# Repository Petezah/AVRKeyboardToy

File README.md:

AVR Keyboard Toy
================

This is beginning as a fork of TinyBasic Plus, whose description
is below.  The intention is to build a self-contained computer-in-
a-keyboard device using an old PS/2 Keyboard and an AVR-based
microcontroller board, outputting display output to a visual display
output--in my case, a 160x160 SPI TFT display.  

The description for TinyBasic Plus is as follows:

# TinyBasic Plus

A C implementation of Tiny Basic, with a focus on support for
Arduino.  It was originally written by Gordon Brandly in the form
of "68000 Tiny Basic", and then ported to C by Michael Field as
"Arduino Basic", though still called "Tiny Basic" in the source
files.

TinyBasic Plus is an extension and modification upon the original
"Tiny Basic" by adding support for a few more devices, configurable
at build time.  It is designed for use on the Arduino, although
builds will soon be easily possible for other platforms through
command line makefiles.  Provided is a makefile that builds for 
unix-ey type OSes.  It has only been tested for Darwin (OS X).

Features added include support for fileio (SD Library), autorunning
a program from the SD card, smaller footprint (PROGMEM), support
for pin data IO, and support for the on-chip EEProm storage for your
program. 

# Full list of supported statements and functions

## System
- BYE		- *exits Basic, soft reboot on Arduino*
- END 		- *stops execution from the program, also "STOP"*
- MEM		- *displays memory usage statistics*
- NEW		- *clears the current program*
- RUN		- *executes the current program*

## File IO/SD Card
- FILES		- 	*lists the files on the SD card*
- LOAD filename.bas	- *loads a file from the SD card*
- CHAIN filename.bas - *equivalent of: new, load filename.bas, run*
- SAVE filename.bas	- *saves the current program to the SD card, overwriting*

## EEProm - nonvolatile on-chip storage
- EFORMAT	- clears the EEProm memory
- ELOAD		- load the program in from EEProm
- ESAVE		- save the current program to the EEProm
- ELIST		- print out the contents of EEProm
- ECHAIN	- load the program from EEProm and run it

## IO, Documentation
- PEEK( address )	- *get a value in memory* (unimplemented)
- POKE address		- *set a value in memory* (unimplemented)
- PRINT expression	- *print out the expression, also "?"*
- REM stuff		- *remark/comment, also "'"*

## Expressions, Math
- A=V, LET A=V	- *assign value to a variable*
- +, -, \*, / - *Math*
- <,<=,=,<>,!=,>=,> - *Comparisons*
- ABS( expression )  - *returns the absolute value of the expression*
- RSEED( v ) - *sets the random seed to v*
- RND( m ) - *returns a random number from 0 to m*

## Control
- IF expression statement - *perform statement if expression is true*
- FOR variable = start TO end	- *start for block*
- FOR variable = start TO end STEP value - *start for block with step*
- NEXT - *end of for block*
- GOTO linenumber - *continue execution at this line number*
- GOSUB linenumber - *call a subroutine at this line number*
- RETURN	- *return from a subroutine*

## Pin IO 
- DELAY	timems*- wait (in milliseconds)*
- DWRITE pin,value - *set pin with a value (HIGH,HI,LOW,LO)*
- AWRITE pin,value - *set pin with analog value (pwm) 0..255*
- DREAD( pin ) - *get the value of the pin* 
- AREAD( analogPin ) - *get the value of the analog pin*

NOTE: "PINMODE" command removed as of version 0.11

## Sound - Piezo wired with red/+ on pin 5 and black/- to ground
- TONE freq,timems - play "freq" for "timems" milleseconds (1000 = 1 second)
- TONEW freq,timems - same as above, but also waits for it to finish
- NOTONE - stop playback of all playing tones

NOTE: TONE commands are by default disabled

# Example programs

Here are a few example programs to get you started...

## Blink

hook up an LED between pin 3 and ground

	10 FOR A=0 TO 10
	20 DWRITE 3, HIGH
	30 DELAY 250
	40 DWRITE 3, LOW
	50 DELAY 250
	60 NEXT A

## Fade

hook up an LED between pin 3 and ground

	10 FOR A=0 TO 10
	20 FOR B=0 TO 255
	30 AWRITE 3, B
	40 DELAY 10
	50 NEXT B
	60 FOR B=255 TO 0 STEP -1
	70 AWRITE 3, B
	80 DELAY 10
	90 NEXT B
	100 NEXT A

## LED KNOB

hook up a potentiometeter between analog 2 and ground, led from digital 3 and ground.  If knob is at 0, it stops

	10 A = AREAD( 2 )
	20 PRINT A
	30 B = A / 4
	40 AWRITE 3, B
	50 IF A == 0 GOTO 100
	60 GOTO 10
	100 PRINT "Done."

## ECHAIN example

Write a small program, store it in EEPROM.  We'll show that variables don't
get erased when chaining happens

	EFORMAT
	10 A = A + 2
	20 PRINT A
	30 PRINT "From eeprom!"
	40 IF A = 12 GOTO 100
	50 PRINT "Shouldn't be here."
	60 END
	100 PRINT "Hi!"

Then store it in EEProm

	ESAVE

Now, create a new program in main memory and run it

	NEW
	10 A = 10
	20 PRINT A
	30 PRINT "From RAM!"
	40 ECHAIN

List both, and run

	ELIST
	LIST
	RUN

# Device Support
## Current
- Arduino - ATMega 168 (~100 bytes available)
- Arduino - ATMega 368 (~1100 bytes available)
- SD cards (via SD Library, for FILES, LOAD, SAVE commands, uses 9k of ROM)
- EEProm (via EEProm Library, uses 500 bytes of ROM)
- Serial IO - command console

## Future
- PS2 Keyboard for standalone use (maybe)
- Graphics support via common function names and ANSI/ReGIS escape codes

# Known Quirks and Limitations
- If LOAD or SAVE are called, FILES fails subsequent listings
- SD cards are not hot-swappable. A reset is required between swaps.

# Authors and Contributors

- Tiny Basic 68k - Gordon Brandly [Project Page (via archive.org)](https://web.archive.org/web/20170306113457/http://members.shaw.ca:80/gbrandly/68ktinyb.html)
- Arduino Basic / Tiny Basic C - Michael Field [Project Page](http://hamsterworks.co.nz/mediawiki/index.php/Arduino_Basic)
- Tiny Basic Plus - Scott Lawrence <yorgle@gmail.com> [Github Page](http://github.com/BleuLlama/TinyBasicPlus)

- Jurg Wullschleger - Fix for unary operations and whitespace in expressions

- AVR Keyboard Toy - Peter Dunshee <peterdun@outlook.com> [Github Page](https://github.com/Petezah/AVRKeyboardToy)

# Links
- [Arduino Microcontroller](http://arduino.cc)

# MIT License

Copyright (c) 2012-2013

Permission is hereby granted, free of charge, to any person obtaining a copy of this software and associated documentation files (the "Software"), to deal in the Software without restriction, including without limitation the rights to use, copy, modify, merge, publish, distribute, sublicense, and/or sell copies of the Software, and to permit persons to whom the Software is furnished to do so, subject to the following conditions:

The above copyright notice and this permission notice shall be included in all copies or substantial portions of the Software.

THE SOFTWARE IS PROVIDED "AS IS", WITHOUT WARRANTY OF ANY KIND, EXPRESS OR IMPLIED, INCLUDING BUT NOT LIMITED TO THE WARRANTIES OF MERCHANTABILITY, FITNESS FOR A PARTICULAR PURPOSE AND NONINFRINGEMENT. IN NO EVENT SHALL THE AUTHORS OR COPYRIGHT HOLDERS BE LIABLE FOR ANY CLAIM, DAMAGES OR OTHER LIABILITY, WHETHER IN AN ACTION OF CONTRACT, TORT OR OTHERWISE, ARISING FROM, OUT OF OR IN CONNECTION WITH THE SOFTWARE OR THE USE OR OTHER DEALINGS IN THE SOFTWARE.

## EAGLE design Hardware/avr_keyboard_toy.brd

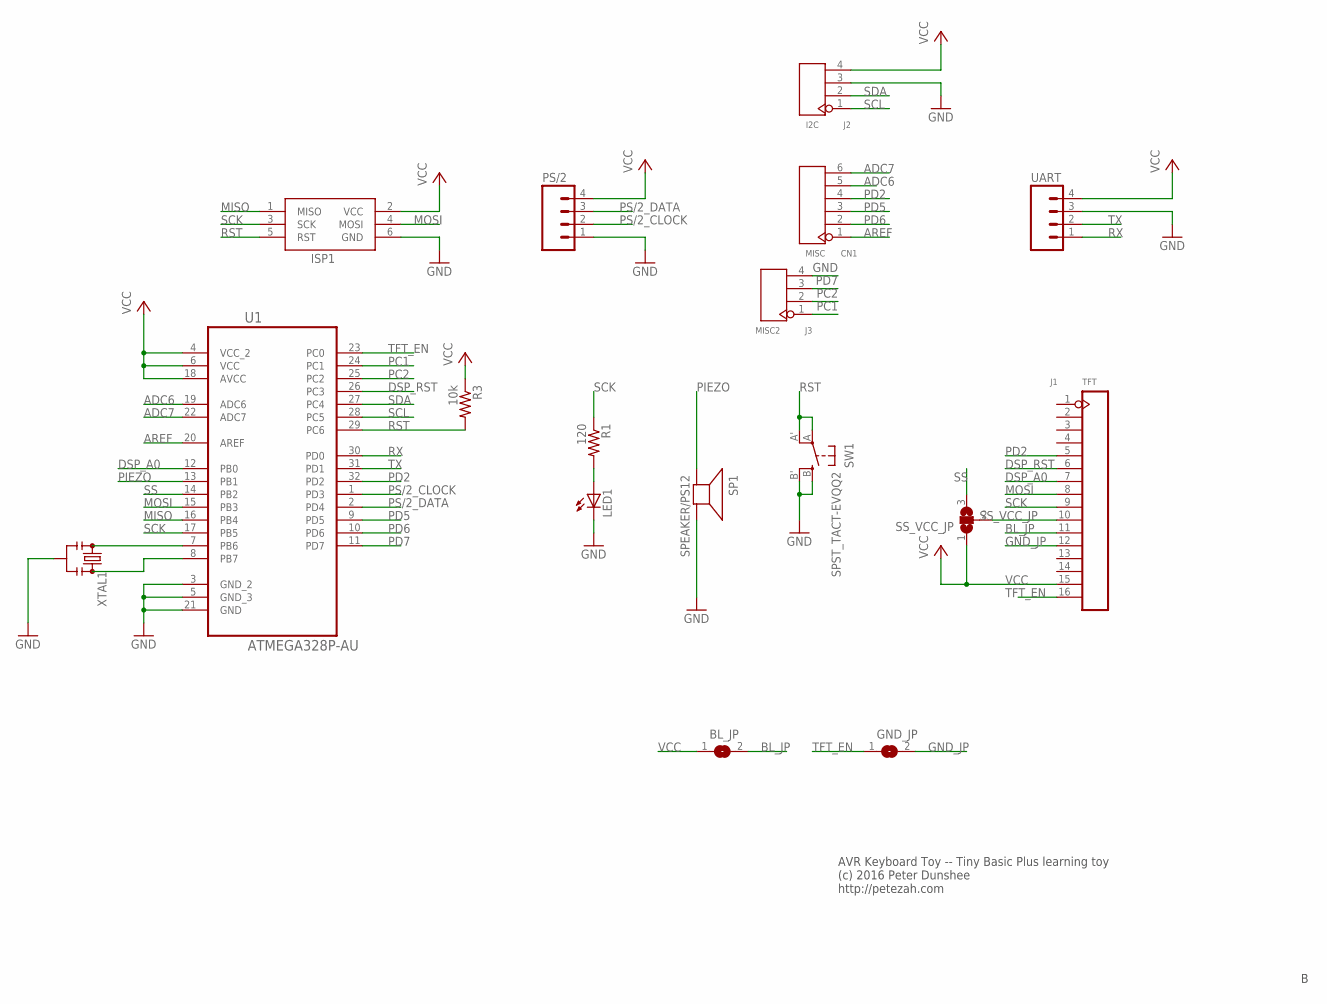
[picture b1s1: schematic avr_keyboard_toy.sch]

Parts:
BL_JP: SJ
CN1: MISC; H6-2.54
GND_JP: SJ
ISP1: AVRISP-6; AVRISP
J1: TFT; H16-2.54
J2: I2C; H4-2.54
J3: MISC2; H4-2.54
LED1: LEDCHIPLED_1206; CHIPLED_1206
PS/2: M04PTH; 1X04
R1: 120; R1206
R3: 10k; R1206
SP1: SPEAKER/PS12; PS12
SS_VCC_JP: SJ2W; SJ_2
SW1: SPST_TACT-EVQQ2; EVQ-Q2
U1: ATMEGA328P-AU; QFP80P900X900X120-32N
UART: M04PTH; 1X04
XTAL1: RESONATORPTH; RESONATOR-PTH

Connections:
ADC6: CN1.5, U1.19 (ADC6)
ADC7: CN1.6, U1.22 (ADC7)
AREF: CN1.1, U1.20 (AREF)
BL_JP: BL_JP.2, J1.11
DSP_A0: J1.7, U1.12 (PB0)
DSP_RST: J1.6, U1.26 (PC3)
GND: ISP1.6 (GND), J2.3, J3.4, LED1.C, PS/2.1, SP1.P$2 (-), SW1.B (S), SW1.B' (S1), U1.3 (GND_2), U1.5 (GND_3), U1.21 (GND), UART.3, XTAL1.2
GND_JP: GND_JP.2, J1.12
MISO: ISP1.1 (MISO), U1.16 (PB4)
MOSI: ISP1.4 (MOSI), J1.8, U1.15 (PB3)
unnamed: U1.7 (PB6), XTAL1.1
unnamed: U1.8 (PB7), XTAL1.3
unnamed: LED1.A, R1.2
PC1: J3.1, U1.24 (PC1)
PC2: J3.2, U1.25 (PC2)
PD2: CN1.4, J1.5, U1.32 (PD2)
PD5: CN1.3, U1.9 (PD5)
PD6: CN1.2, U1.10 (PD6)
PD7: J3.3, U1.11 (PD7)
PIEZO: SP1.P$1 (+), U1.13 (PB1)
PS/2_CLOCK: PS/2.2, U1.1 (PD3)
PS/2_DATA: PS/2.3, U1.2 (PD4)
RST: ISP1.5 (RST), R3.2, SW1.A, SW1.A' (P1), U1.29 (PC6)
RX: U1.30 (PD0), UART.1
SCK: ISP1.3 (SCK), J1.9, R1.1, U1.17 (PB5)
SCL: J2.1, U1.28 (PC5)
SDA: J2.2, U1.27 (PC4)
SS: SS_VCC_JP.3, U1.14 (PB2)
SS_VCC_JP: J1.10, SS_VCC_JP.2
TFT_EN: GND_JP.1, J1.16, U1.23 (PC0)
TX: U1.31 (PD1), UART.2
VCC: BL_JP.1, ISP1.2 (VCC), J1.15, J2.4, PS/2.4, R3.1, SS_VCC_JP.1, U1.4 (VCC_2), U1.6 (VCC), U1.18 (AVCC), UART.4

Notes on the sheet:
AVR Keyboard Toy -- Tiny Basic Plus learning toy (c) 2016 Peter Dunshee http://petezah.com

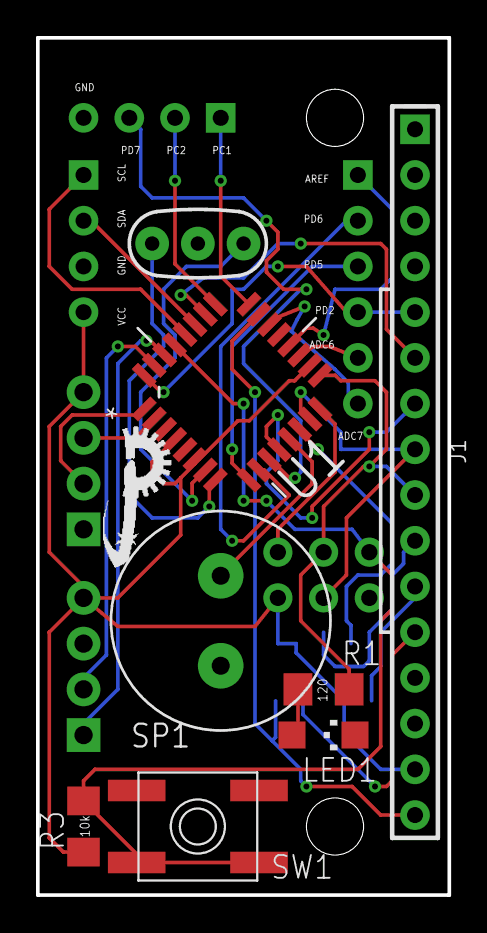
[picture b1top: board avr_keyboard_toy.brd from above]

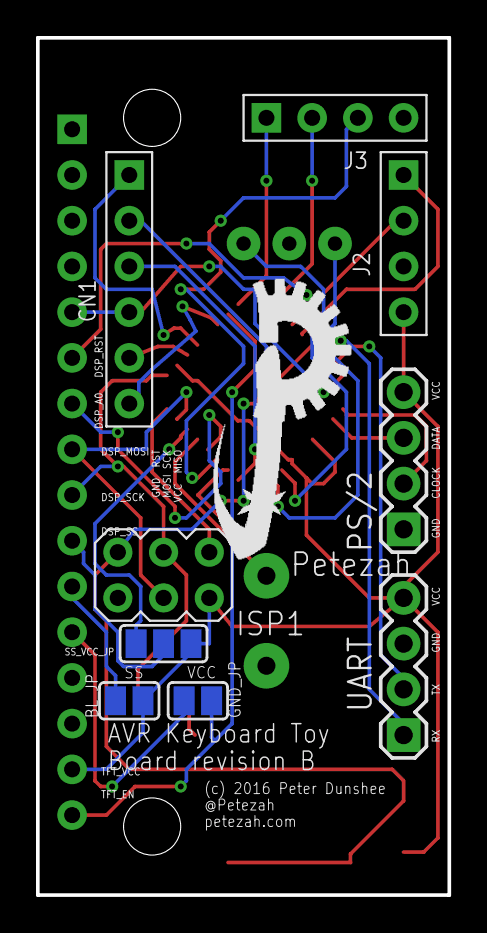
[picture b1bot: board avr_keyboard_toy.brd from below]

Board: 2 copper layers, 22.9 x 47.6 mm, 19 parts (10 on the bottom side), 32 nets.

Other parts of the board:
U$1: LOGO_TINY
U$2: LOGO_SM

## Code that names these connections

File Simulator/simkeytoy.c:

/*
 charlcd.c

 Copyright Luki <humbell@ethz.ch>
 Copyright 2011 Michel Pollet <buserror@gmail.com>
 Copyright 2014 Doug Szumski <d.s.szumski@gmail.com>

 This file is part of simavr.

 simavr is free software: you can redistribute it and/or modify
 it under the terms of the GNU General Public License as published by
 the Free Software Foundation, either version 3 of the License, or
 (at your option) any later version.

 simavr is distributed in the hope that it will be useful,
 but WITHOUT ANY WARRANTY; without even the implied warranty of
 MERCHANTABILITY or FITNESS FOR A PARTICULAR PURPOSE.  See the
 GNU General Public License for more details.

 You should have received a copy of the GNU General Public License
 along with simavr.  If not, see <http://www.gnu.org/licenses/>.
 */

#include <stdlib.h>
#include <stdio.h>
#include <string.h>
#include <libgen.h>
#include <signal.h>

#include "sim_avr.h"
#include "avr_ioport.h"
#include "sim_elf.h"
#include "sim_gdb.h"
#include "sim_hex.h"

#if __APPLE__
#include <GLUT/glut.h>
#else
#include <GL/glut.h>
#endif

#include <pthread.h>

#include "st7735_glut.h"
//#include "st7735_virt.h"
#include "uart_stdin.h"

int window_identifier;

avr_t * avr = NULL;
st7735_t st7735;
uart_stdin_t uart_stdin;

static void *
avr_run_thread (void * ignore)
{
	while (1)
	{
		avr_run (avr);
	}
	return NULL;
}

//int bitbanging = 0;

/* Called on a key press */
void
keyCB (unsigned char key, int x, int y)
{
	//printf("keypress %02x\n", key);
	switch (key)
	{
		case 0x1B: // ESC
			exit (0);
			break;
		case '`':
			avr->gdb_port = 1234;
			avr_gdb_init(avr);
			break;
		default:
			uart_stdin_inject(&uart_stdin, key);
			break;
	}
}

/* Function called whenever redisplay needed */

void
displayCB (void)
{
	glClear (GL_COLOR_BUFFER_BIT | GL_DEPTH_BUFFER_BIT);
	// Select modelview matrix
	glMatrixMode (GL_MODELVIEW);
	glPushMatrix ();
	// Start with an identity matrix
	glLoadIdentity ();
	st7735_gl_draw (&st7735);
	glPopMatrix ();
	glutSwapBuffers ();
}

// gl timer. if the lcd is dirty, refresh display
void
timerCB (int i)
{
	// restart timer
	glutTimerFunc (1000 / 100, timerCB, 0);
	glutPostRedisplay ();
}

int
initGL (int w, int h, float pix_size)
{
	w *= pix_size;
	h *= pix_size;

	// Double buffered, RGB disp mode.
	glutInitDisplayMode (GLUT_RGB | GLUT_DOUBLE);
	glutInitWindowSize (w * 4, h * 4);
	window_identifier = glutCreateWindow ("ST7735 128x160 TFT");

	// Set up projection matrix
	glMatrixMode (GL_PROJECTION);
	// Start with an identity matrix
	glLoadIdentity ();
	glOrtho (0, w, 0, h, 0, 10);
	glScalef (1, -1, 1);
	glTranslatef (0, -1 * h, 0);

	// Set window's display callback
	glutDisplayFunc (displayCB);
	// Set window's key callback
	glutKeyboardFunc (keyCB);

	glutTimerFunc (1000 / 24, timerCB, 0);

	st7735_gl_init (pix_size);

	return 1;
}

void
sig_int(
	int sign)
{
	printf("signal caught, simavr terminating\n");
	if (avr)
		avr_terminate(avr);
	exit(0);
}

int
main (int argc, char *argv[])
{
	elf_firmware_t f = { { 0 } };
	const char * fname = "AvrKeyboardToy.hex";
	char path[256];
	uint32_t loadBase = AVR_SEGMENT_OFFSET_FLASH;
	sprintf (path, "%s/%s", dirname (argv[0]), fname);
	printf ("Firmware pathname is %s\n", path);
	
	//elf_read_firmware (fname, &f);
	ihex_chunk_p chunk = NULL;
	int cnt = read_ihex_chunks(fname, &chunk);
	if (cnt <= 0) {
		fprintf(stderr, "%s: Unable to load IHEX file %s\n",
			argv[0], fname);
		exit(1);
	}
	printf("Loaded %d section of ihex\n", cnt);
	for (int ci = 0; ci < cnt; ci++)
	{
		if (chunk[ci].baseaddr < (1 * 1024 * 1024)) 
		{
			f.flash = chunk[ci].data;
			f.flashsize = chunk[ci].size;
			f.flashbase = chunk[ci].baseaddr;
			printf("Load HEX flash %08x, %d\n", f.flashbase, f.flashsize);
		}
		else if (chunk[ci].baseaddr >= AVR_SEGMENT_OFFSET_EEPROM ||
			chunk[ci].baseaddr + loadBase >= AVR_SEGMENT_OFFSET_EEPROM)
		{
			// eeprom!
			f.eeprom = chunk[ci].data;
			f.eesize = chunk[ci].size;
			printf("Load HEX eeprom %08x, %d\n", chunk[ci].baseaddr, f.eesize);
		}
	}

	// Hard-coded frequency and mcu
	strcpy(f.mmcu, "atmega328");
	f.frequency = 8000000;

	printf ("firmware %s f=%d mmcu=%s\n", fname, (int) f.frequency, f.mmcu);

	avr = avr_make_mcu_by_name (f.mmcu);
	if (!avr)
	{
		fprintf (stderr, "%s: AVR '%s' not known\n", argv[0], f.mmcu);
		exit (1);
	}

	printf("init avr\n");
	avr_init (avr);
	printf("loading avr firmware\n");
	avr_load_firmware (avr, &f);

	st7735_init (avr, &st7735, 128, 64);

	// ST7735 wired to the SPI bus, with the following additional pins:
	// CS=10   -> PB2
	// RST=17  -> PC3
	// DC=8    -> PB0
	// SCK=13  -> PB5
	// MOSI=11 -> PB3
	st7735_wiring_t wiring =
	{
		.chip_select.port = 'B',
		.chip_select.pin = 2,
		.data_instruction.port = 'B',
		.data_instruction.pin = 0,
		.reset.port = 'C',
		.reset.pin = 3,
	};

	st7735_connect (&st7735, &wiring);

	// PS/2 keyboard is wired to CLK->D3, DATA->D4;
	// At some point we can revisit that; for now
	// we inject over virtual UART
	uart_stdin_init(avr, stdout, &uart_stdin);
	uart_stdin_connect(&uart_stdin, '0');

	printf ("ST7735 display demo\n   Press 'q' to quit\n");

	// Initialize GLUT system
	glutInit (&argc, argv);
	initGL (ST7735_VIRT_COLS, ST7735_VIRT_ROWS, 0.5);// (ssd1306.columns, ssd1306.rows, 0.5);

	// Trace settings, if necessary
    //avr->trace = 1;
	avr->log = 3;

	pthread_t run;
	pthread_create (&run, NULL, avr_run_thread, NULL);

	glutMainLoop ();

	// even if not setup at startup, activate gdb if crashing
	//avr->gdb_port = 1234;
	//if (gdb) {
	//	avr->state = cpu_Stopped;
	//	avr_gdb_init(avr);
	//}

	// signal(SIGINT, sig_int);
	// signal(SIGTERM, sig_int);

	// for (;;) {
	// 	int state = avr_run(avr);
	// 	if (state == cpu_Done || state == cpu_Crashed)
	// 		break;
	// }

	// avr_terminate(avr);
}

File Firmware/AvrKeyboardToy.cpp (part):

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
// Display utilities
#define TFT_CS 10
#define TFT_RST 17 // PC3=D17=A3
#define TFT_DC 8

#define TFT_EN 14

#elif defined(AVR_KEYBOARD_TOY_TEST)

// Display utilities
#define TFT_CS 17 // PC3=D17=A3
#define TFT_RST 2 // PD2
#define TFT_DC 8

#define TFT_EN 14

#else
#error No board type was defined!  Must define either AVR_KEYBOARD_TOY_RELEASE or AVR_KEYBOARD_TOY_TEST!
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#define TFT_MOSI 11
////

// NB: Tone speaker uses D9/PB1

// Special, serial-only commands
#define CURS_UP CTRLW
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    //g_display.setRotation(2); // 180* rotation

    // Power on the display
    //pinMode(TFT_EN, OUTPUT);
    //digitalWrite(TFT_EN, LOW); // TFT is enabled LOW
    m_displayEnabled = true;
}
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
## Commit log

2016-04-29 Fix compile errors
2016-05-04 Added conditional support for output on an ST7735 based SPI display. Also added a new BASIC command to manipulate the background color--not to be considered done though.
2016-05-27 Fix character deleting. Removed magic numbers. * Added a parameter to outchar to suppress display output for cases where the output will differ from Serial * Replaced magic numbers with #defines for 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
2016-05-27 A blinking cursor for the display.
2016-05-27 Update Readme
    Added description to explain the intent of this fork
2016-05-27 Update Readme with new project link
2016-05-27 Added keyboard support; not sure why the Serial library interacts with the keyboard one. Serial is commented out in the key spot for now; will investigate later.
2016-05-28 PS2KeyAdvanced library is *way* more reliable, and deterministic. Also way more complicated--not necessarily a bad thing. REPL is broken now though because I'm not translating non-printable chars cor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
2016-05-29 Added a keyboard utility to separate out PS/2 key event translation. Implemented just enough to see it working in tiny basic
2016-06-12 Translated all non-shifted keys
2016-06-12 Translate shifted/special characters
2016-06-17 Set the SD ss to something else, but there is some interaction going on, so disabling again for now. I will fix later on possibly, once I simplify this program.
2016-06-17 Initial work on schematic
2016-06-18 All the parts are now on the schematic; now to actually hook them up
2016-06-18 For fun, added commands to drive an I2C port expander
2016-06-18 A bunch of work on the schematic; mostly done
2016-06-19 Power supplies, mostly
2016-06-19 Mostly finished
2016-06-19 Hooked up TFT, SD and MCP to enable pins, so eventually the software can put the whole device to sleep. Brought out the remaining 4 MCU pins to a MISC header.
2016-06-22 Progress on pcb
2016-06-23 Routing signals progress
2016-06-24 Finished routing signals
2016-06-24 Finished layout for rev. A board
2016-07-15 Added working color commands
2016-08-16 Setup commandline build Added all dependencies, including arduino core to the firmware folder, as well as a makefile for building
2016-08-31 Refactoring the project The intent is to let AvrKeyboardToy be the toplevel manager, and TinyBasicPlus, etc, will be subordinate
2016-08-31 Ignore vscode stuff
2016-08-31 Add the simulator to the source tree
2016-08-31 Setup makefiles to create symlinks in the parent
2016-08-31 Master Makefile to make everything
2016-08-31 More things to ignore
2016-08-31 Working on fast char blit In this program, we don't care about overwriting the pixels behind the characters we draw--in fact, that is exactly what we want. drawFastChar simply "blits" the contents of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
2016-08-31 Use the 8x8 font instead I brought over the 8x8 font I exported for the ATiny85 graphics project earlier. It eats up slightly more flash and a couple more X pixels, but lets me optimize the draw rout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
2016-09-11 Tweaks and fixes We don't need a blank line on the bottom of each char, our 8x8 font already has those Also added some display optimizations--IDisplay which allows the buffer to update the display as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
2016-09-11 Makefile now works properly with winavr Just a few tweaks to make it work with just the win-avr toolchain. Upload can now be accomplished with "make upload"
2016-09-11 Display fix and tweak We're going to assemble the device with the screen rotated; so set the rotation on the display. Also, this fixes a bug that only showed up on the actual hardware--the addr windo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
2016-09-11 Fast display refresh Optimizing the display code with a routine that can refresh the whole display in one SPI transaction.
2016-09-17 Display bugs and initial input implementation * A couple off-by one errors in both the display implementation and the simulator * Initial input implementation for keyboard and serial fall-back
2016-09-17 Working on handling serial escape sequences Mostly cursor key movement, to make testing via serial port easier
2016-09-17 Added special serial-mode command chars
2016-09-21 Keyboard cursor keys Handle the PS/2 cursor keys A bit of refactoring also
2016-09-28 Working on integrating TinyBasic WIP integrating TinyBasic into the main firmware program
2016-09-28 BASIC now sort of works * GDB port can now be enabled in the simulator by pressing `. This allowed me to figure out what was wrong with the firmware that was preventing BASIC from running. Essentiall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
2016-10-11 Trying to figure out what is going wrong
2016-10-12 Reworked the interpreter "loop" It executes only one action per update now, and works much better
2016-10-22 Color buffer work, etc Added support for a color buffer to the display buffer, so the buffer can keep track of the color of each character. Also added the SID library, since I intend to make the soun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
2016-10-22 Hook the cursor up to the correct colors
2016-10-23 Fixed the color lookup problem Can't believe that was the issue and the compiler didn't catch that. >:( I think my cflags are set wrong perhaps.
2016-10-23 Fixed fg/bgcolor commands
2016-10-23 Comment out debug lines
2016-10-23 Working on Rev B of hardware
2016-10-26 Added SID test, and made rev B of board
2016-10-26 Fixed silkscreen layers
2016-10-28 Slight changes to the board
2016-10-28 Tweaking the silkscreen a bit
2016-10-28 Fixed a couple labels that were in bad places
2016-10-30 Minor edits
2016-11-08 Made the board a bit more configurable Added jumpers to allow me to configure one board for one display board, and another one for a different one.
2016-11-27 Project cleanup and test board support * Add support to build for the new test board * Cleanup the dependencies in the project a bit--PS/2 lib now uses the interrupt vector directly * Updated the fir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
2016-11-27 Changed the refresh code a bit Also, the SID library is interacting strangely with the PS/2 library. I am disabling it until I track it down.
2016-11-27 Fixed an overrun bug in the display buffer Also implemented the color buffer portion of the scroll up method
2017-01-20 Finish up version 1.0 Removed SID, since it is too much of a performance hog for this implementation. I moved back to using the Tone library Moved the board definitions to the makefile to make it eas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
2018-04-13 Updated eagle files
2018-04-13 Update after merge
2018-04-13 Update port
2018-05-16 Fix global makefile
2018-05-16 Disable sleep mode; it doesn't work
2018-10-30 Add Larry's smart response library
2018-10-30 SRXE port work-in-progress
2018-10-31 Some test code
2018-10-31 Tiny basic now renders
2018-11-02 Fix character translation
2018-11-17 Disable UART (Serial), since we are not using it, and it conflicts with the SRXE keyboard
2018-11-17 Sleep with the F0 key
2020-03-15 Update programming port
2020-06-07 Windows sim
2020-06-07 Working on Windows port
2020-06-07 Update SRXE module
2020-06-14 WIP builds but doesn't link--need to supply some Windows versions of SRXE methods
2020-06-14 WIP windows xc

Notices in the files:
parts and their libraries:
SparkFun-Connectors: Licensing: Creative Commons ShareAlike 4.0 International - https://creativecommons.org/licenses/by-sa/4.0
